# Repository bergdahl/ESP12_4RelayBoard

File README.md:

# ESP12_4RelayBoard

This is a simple ESP-12 based 4 relay board I designed to be used in Home Assistant. It is powered by 5V over a micro USB connector,
and switches loads at up to the rated voltage of the relay - 28V/10A, although I recommend limiting the power to max 6 Amps per channel.
Also, the screw connectors used are rated at maximum 15A, so you need to keep the _total combined_ power usage under that limit.

> NOTE: This PCB is _NOT_ designed to be used for mains voltage!

## PCB files

I have added the Gerber files in the `PCB/Gerber` folder, just zip and upload to your favorite PCB manufacturer.

I have also included the EAGLE design files if you need to modify the design for yoyr needs.

## Firmware

I use ESPHome to set it up, which is the easiest way for it to show up in Home Assistant. 

Change the `esphome` section to this:

```
esphome:
  name: relay1
  platform: ESP8266
  board: esp12e
```
Add the following section to add the relays as switches in Home Assistant.

```
switch:
  - platform: gpio
    name: "Relay1"
    pin: GPIO4
  - platform: gpio
    name: "Relay2"
    pin: GPIO5
  - platform: gpio
    name: "Relay3"
    pin: GPIO12
  - platform: gpio
    name: "Relay4"
    pin: GPIO13
```

### Flashing the board

You will need a USB-Serial adapter for initial upload of the firmware, and use the [ESPHome-Flasher](https://github.com/esphome/esphome-flasher) flashing utility.

 - Compile and download the firmware to your local machine.
 - Connect the serial adapter to the board, the board is designed for the pinout of standard FT232RL adapters.
 - Hold down the BOOT button, tap the RST button and then let go of RST. This puts the ESP-12 module in bootloader mode ready for firmware upload.
 - Start ESPHome-Flasher, select the firmware file and the proper COM port and click _Flash ESP_.

## Enclosure

I designed a simple enclosure for 3D printing, available as STL files in the `Enclosure` folder. 

I also included the Fusion360 design file if you need to modify the design for your usage.

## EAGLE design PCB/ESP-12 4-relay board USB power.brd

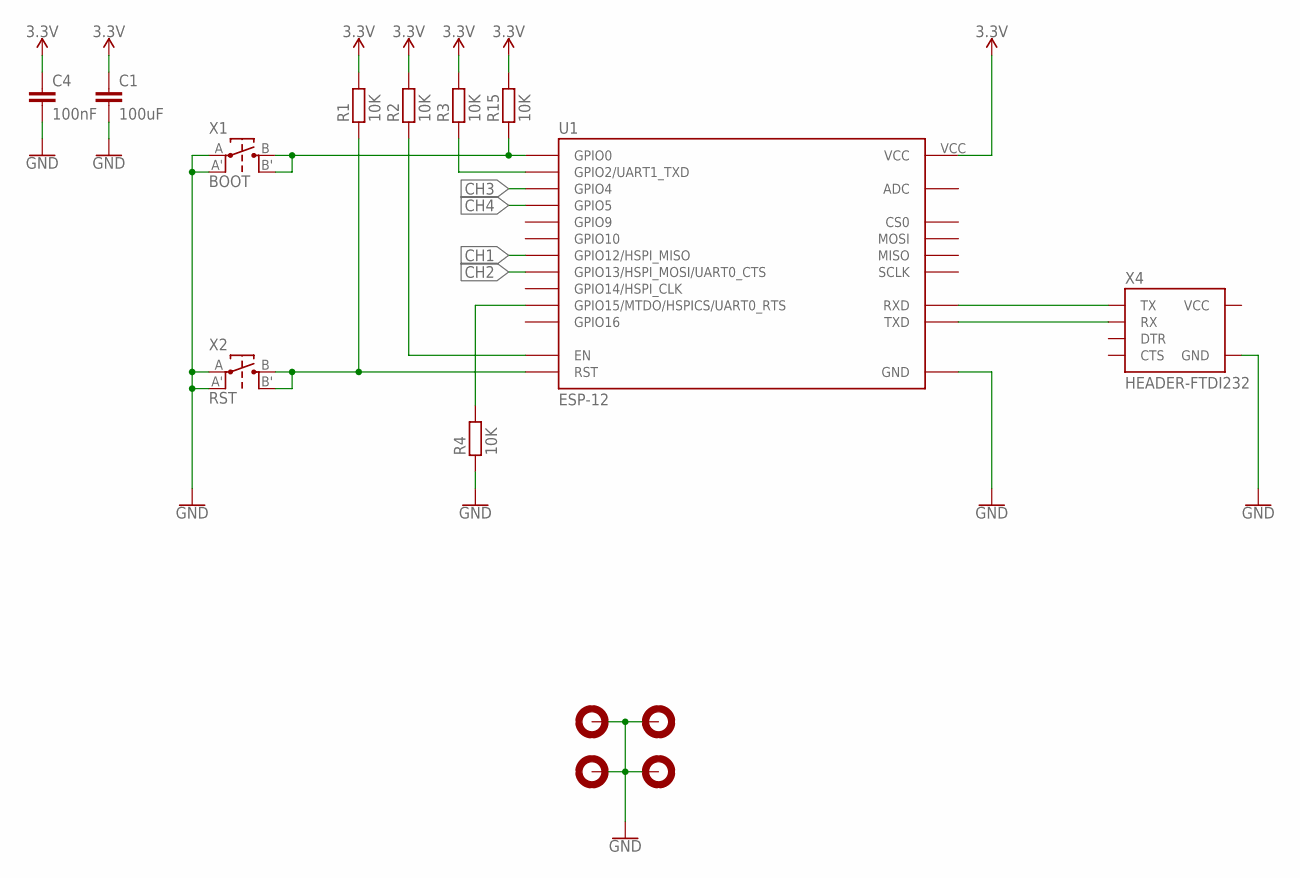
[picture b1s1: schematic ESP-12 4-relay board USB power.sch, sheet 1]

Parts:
C1: 100uF; C0603
C4: 100nF; C0603
H1, H2, H3, H4: MOUNTHOLE-PAD3.2; 3.2-PAD
R1, R2, R3, R4, R15: 10K; R0603
U1: ESP-12; ESP-12E
X1: BOOT; TACT-SWITCH-EVQ
X2: RST; TACT-SWITCH-EVQ
X4: HEADER-FTDI232; FTDI232-1X06

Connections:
3.3V: C1.1, C4.1, R1.2, R2.2, R3.2, R15.2, U1.VCC; also elsewhere on the board
CH1: U1.GPIO12 (GPIO12/HSPI_MISO); also elsewhere on the board
CH2: U1.GPIO13 (GPIO13/HSPI_MOSI/UART0_CTS); also elsewhere on the board
CH3: U1.GPIO4; also elsewhere on the board
CH4: U1.GPIO5; also elsewhere on the board
GND: C1.2, C4.2, H1.B3,2, H2.B3,2, H3.B3,2, H4.B3,2, R4.1, U1.GND, X1.A, X1.A', X2.A, X2.A', X4.GND; also elsewhere on the board
unnamed: R4.2, U1.GPIO15 (GPIO15/MTDO/HSPICS/UART0_RTS)
unnamed: R2.1, U1.EN
unnamed: R1.1, U1.RST, X2.B, X2.B'
unnamed: R15.1, U1.GPIO0, X1.B, X1.B'
unnamed: R3.1, U1.GPIO2 (GPIO2/UART1_TXD)
RXD: U1.RXD, X4.TX
TXD: U1.TXD, X4.RX
VCC: X4.VCC

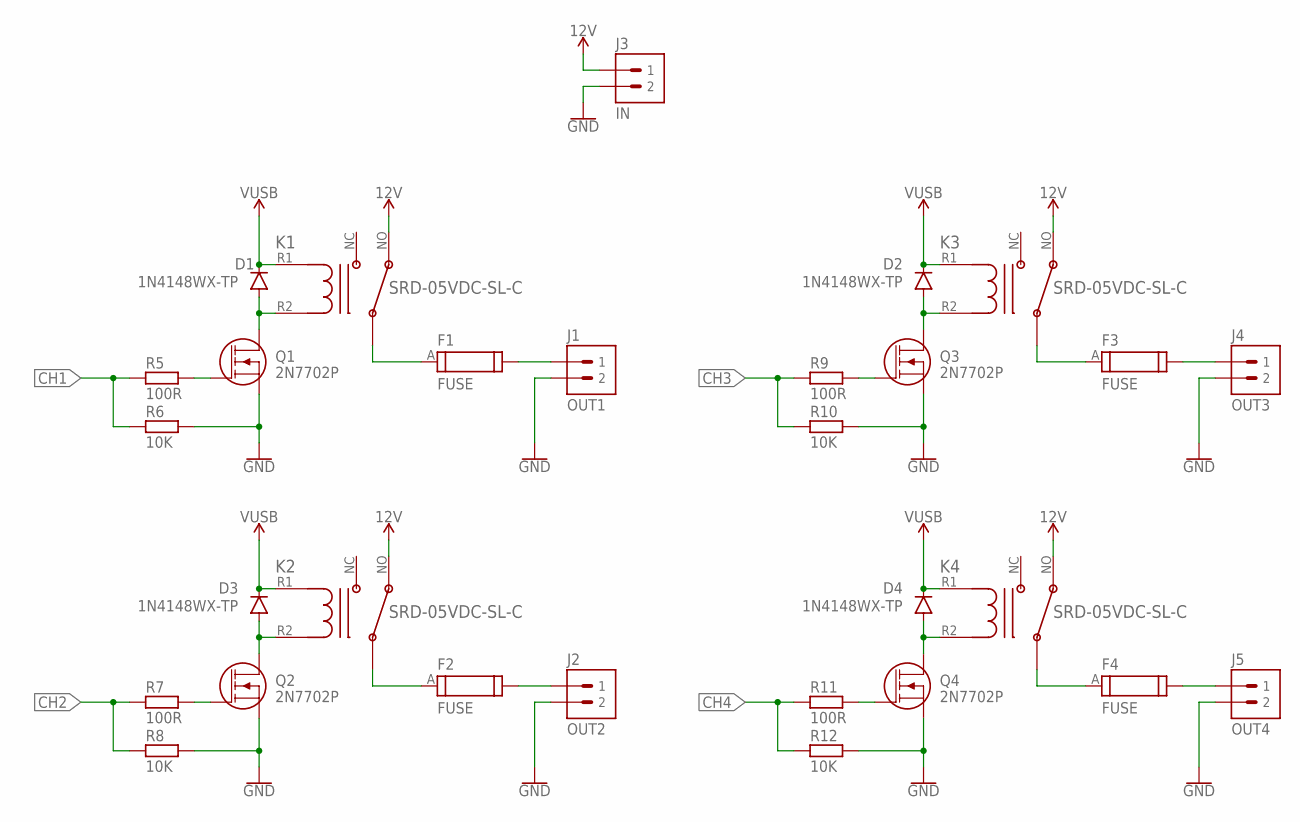
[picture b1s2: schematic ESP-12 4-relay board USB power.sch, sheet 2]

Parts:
D1, D2, D3, D4: 1N4148WX-TP; SOD-323
F1, F2, F3, F4: FUSE; FUSE-TEAL
J1: OUT1; ONSHORE-OSTTC022162
J2: OUT2; ONSHORE-OSTTC022162
J3: IN; ONSHORE-OSTTC022162
J4: OUT3; ONSHORE-OSTTC022162
J5: OUT4; ONSHORE-OSTTC022162
K1, K2, K3, K4: SRD-05VDC-SL-C; RELAY-SRD-05VDC-SL-C
Q1, Q2, Q3, Q4: 2N7702P; SOT23-3
R5, R7, R9, R11: 100R; R0603
R6, R8, R10, R12: 10K; R0603

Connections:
12V: J3.1, K1.NO (NC), K2.NO (NC), K3.NO (NC), K4.NO (NC)
CH1: R5.1, R6.1; also elsewhere on the board
CH2: R7.1, R8.1; also elsewhere on the board
CH3: R9.1, R10.1; also elsewhere on the board
CH4: R11.1, R12.1; also elsewhere on the board
GND: J1.2, J2.2, J3.2, J4.2, J5.2, Q1.2 (S), Q2.2 (S), Q3.2 (S), Q4.2 (S), R6.2, R8.2, R10.2, R12.2; also elsewhere on the board
unnamed: D1.2 (A), K1.R2, Q1.3 (D)
unnamed: F1.A, K1.C
unnamed: F1.B, J1.1
unnamed: Q1.1 (G), R5.2
unnamed: D3.2 (A), K2.R2, Q2.3 (D)
unnamed: Q2.1 (G), R7.2
unnamed: F2.A, K2.C
unnamed: F2.B, J2.1
unnamed: D2.2 (A), K3.R2, Q3.3 (D)
unnamed: F3.A, K3.C
unnamed: F3.B, J4.1
unnamed: Q3.1 (G), R9.2
unnamed: D4.2 (A), K4.R2, Q4.3 (D)
unnamed: Q4.1 (G), R11.2
unnamed: F4.A, K4.C
unnamed: F4.B, J5.1
VUSB: D1.1 (C), D2.1 (C), D3.1 (C), D4.1 (C), K1.R1, K2.R1, K3.R1, K4.R1; also elsewhere on the board

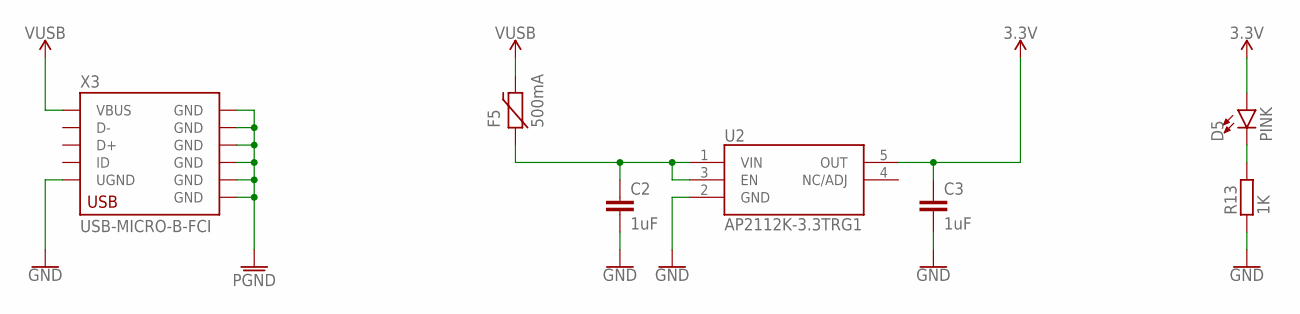
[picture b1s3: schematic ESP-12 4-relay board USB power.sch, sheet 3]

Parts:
C2, C3: 1uF; C0603
D5: PINK; LED0603
F5: 500mA; PTC-0ZCJ-1206
R13: 1K; R0603
U2: AP2112K-3.3TRG1; SOT23-5
X3: USB-MICRO-B-FCI

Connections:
3.3V: C3.1, D5.A, U2.5 (OUT); also elsewhere on the board
GND: C2.2, C3.2, R13.1, U2.2 (GND), X3.5 (UGND); also elsewhere on the board
unnamed: D5.C, R13.2
unnamed: C2.1, F5.1, U2.1 (VIN), U2.3 (EN)
PGND: X3.GND@1 (GND), X3.GND@2 (GND), X3.GND@3 (GND), X3.GND@4 (GND), X3.GND@5 (GND), X3.GND@6 (GND)
VUSB: F5.2, X3.1 (VBUS); also elsewhere on the board

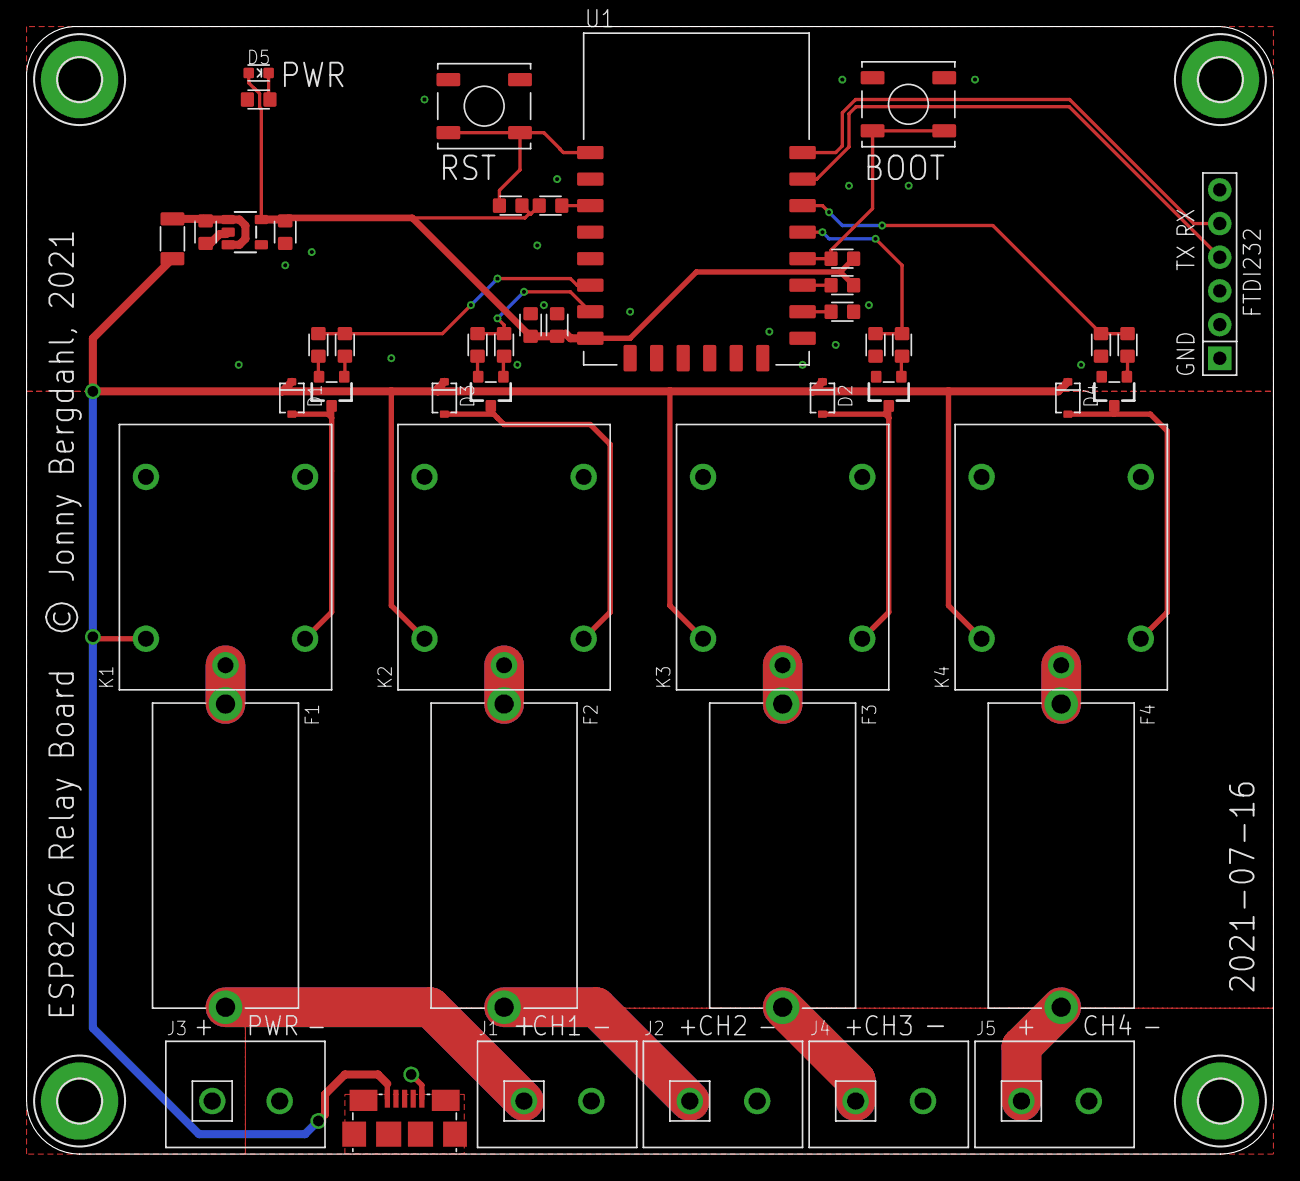
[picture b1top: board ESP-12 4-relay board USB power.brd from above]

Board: 2 copper layers, 94.0 x 85.0 mm, 51 parts (0 on the bottom side), 34 nets.

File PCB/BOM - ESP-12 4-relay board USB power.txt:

Qty Value            Device                        Package              Parts                                 Description                                                                                   
4   100R             RESISTOR0603                  R0603                R5, R7, R9, R11                                                                                                                     
1   100nF            CAPC0603                      C0603                C4                                                                                                                                  
1   100uF            CAPC0603                      C0603                C1                                                                                                                                  
9   10K              RESISTOR0603                  R0603                R1, R2, R3, R4, R6, R8, R10, R12, R15                                                                                               
1   1K               RESISTOR0603                  R0603                R13                                                                                                                                 
4   1N4148WX-TP      DIODE1N4148WX-TP              SOD-323              D1, D2, D3, D4                                                                                                                      
2   1uF              CAPC0603                      C0603                C2, C3                                                                                                                              
4   2N7702P          MOSFET-NCHSOT23-3             SOT23-3              Q1, Q2, Q3, Q4                                                                                                                      
1   500mA            PTC0ZCJ                       PTC-0ZCJ-1206        F5                                                                                                                                  
1   AP2112K-3.3TRG1  REGULATOR-AP2112KK-SOT23-5    SOT23-5              U2                                                                                                                                  
1   BOOT             TACT-SWITCHEVQ                TACT-SWITCH-EVQ      X1                                                                                                                                  
1   ESP-12           ESP-12E                       ESP-12E              U1                                                                                                                                  
4   FUSE             FUSETEAL                      FUSE-TEAL            F1, F2, F3, F4                        https://www.aliexpress.com/item/1005001704678944.html                                                                                              
1   HEADER-FTDI232   HEADER-FTDI232                FTDI232-1X06         X4                                                                                                                                  
1   IN               TERMINAL-1X02-5.08OSTTC022162 ONSHORE-OSTTC022162  J3                                    https://www.digikey.se/product-detail/sv/on-shore-technology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 
4   MOUNTHOLE-PAD3.2 MOUNTHOLE-PAD3.2              3.2-PAD              H1, H2, H3, H4                                                                                                                      
1   OUT1             TERMINAL-1X02-5.08OSTTC022162 ONSHORE-OSTTC022162  J1                                    https://www.digikey.se/product-detail/sv/on-shore-technology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 
1   OUT2             TERMINAL-1X02-5.08OSTTC022162 ONSHORE-OSTTC022162  J2                                    https://www.digikey.se/product-detail/sv/on-shore-technology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 
1   OUT3             TERMINAL-1X02-5.08OSTTC022162 ONSHORE-OSTTC022162  J4                                    https://www.digikey.se/product-detail/sv/on-shore-technology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 
1   OUT4             TERMINAL-1X02-5.08OSTTC022162 ONSHORE-OSTTC022162  J5                                    https://www.digikey.se/product-detail/sv/on-shore-technology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 
1   PINK             LED0603                       LED0603              D5                                    LED (Generic)                                                                                 
1   RST              TACT-SWITCHEVQ                TACT-SWITCH-EVQ      X2                                    https://www.digikey.se/product-detail/sv/panasonic-electroni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
4   SRD-05VDC-SL-C   RELAYSRD-05VDC-SL-C           RELAY-SRD-05VDC-SL-C K1, K2, K3, K4                        https://www.aliexpress.com/wholesale?SearchText=SRD-05VDC-SL-C
1   USB-MICRO-B-FCI  USB-MICRO-B-FCI               USB-MICRO-B-FCI      X3                                    https://www.digikey.se/product-detail/sv/amphenol-icc-fci/10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

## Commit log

2021-07-21 Fix wrong image
2021-07-22 Switch NC and NO on relays
2021-07-29 New enclosure
2021-07-29 Fix README
2021-08-11 Add PDF file

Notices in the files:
PCB/ESP-12 4-relay board USB power.brd:
© Jonny Bergdahl, 2021
